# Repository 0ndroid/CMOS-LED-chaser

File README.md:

# CMOS-LED-chaser
LED chaser board with control logic built of discrete transistors

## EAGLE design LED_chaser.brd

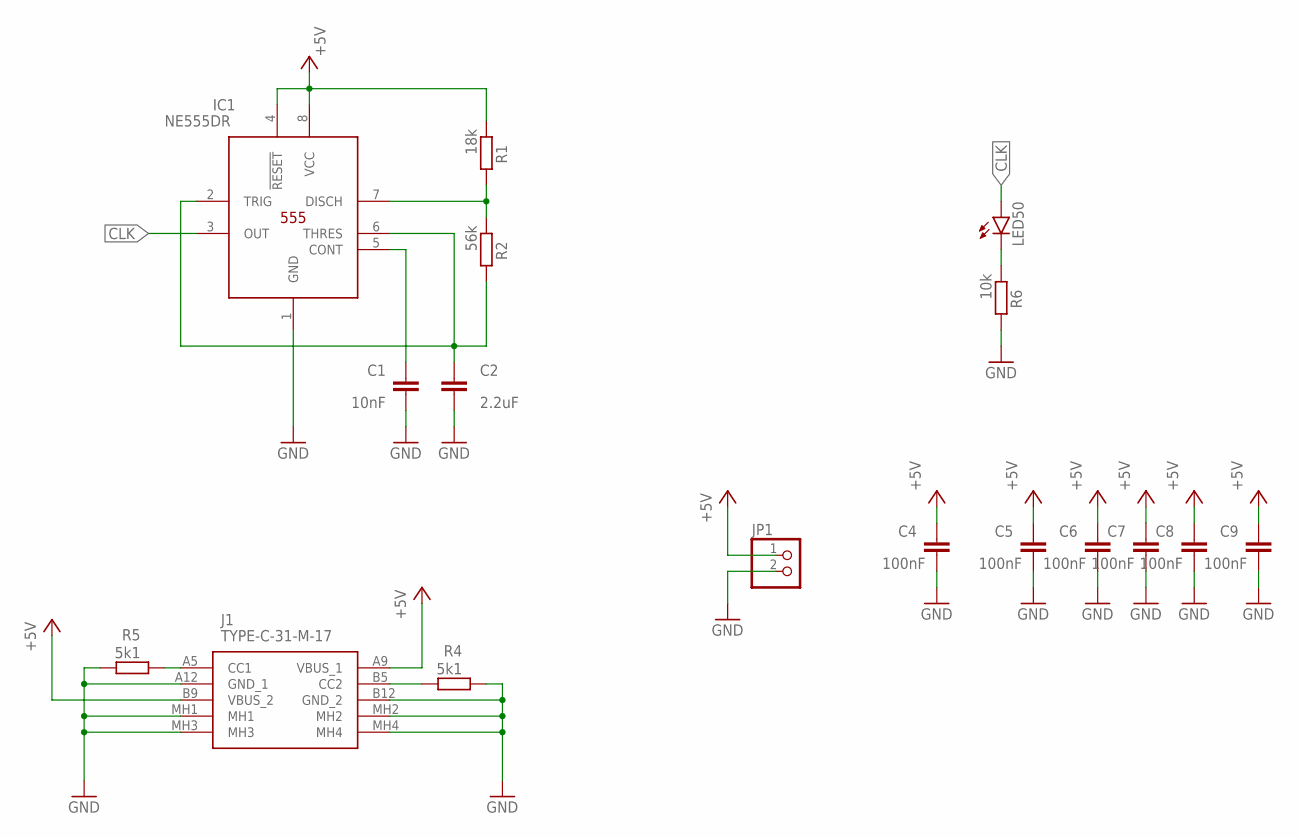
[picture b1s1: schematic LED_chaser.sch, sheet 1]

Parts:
C1: 10nF; C0603
C2: 2.2uF; C0603
C4, C5, C6, C7, C8, C9: 100nF; C0603
IC1: NE555DR; SOIC127P600X175-8N
J1: TYPE-C-31-M-17; TYPEC31M17
JP1: PINHD-1X2; 1X02
LED50: LEDCHIP-LED0603; CHIP-LED0603
R1: 18k; R0603
R2: 56k; R0603
R4, R5: 5k1; R0603
R6: 10k; R0603

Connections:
+5V: C4.1, C5.1, C6.1, C7.1, C8.1, C9.1, IC1.4 (!RESET), IC1.8 (VCC), J1.A9 (VBUS_1), J1.B9 (VBUS_2), JP1.1, R1.1; also elsewhere on the board
CLK: IC1.3 (OUT), LED50.A; also elsewhere on the board
GND: C1.2, C2.2, C4.2, C5.2, C6.2, C7.2, C8.2, C9.2, IC1.1 (GND), J1.A12 (GND_1), J1.B12 (GND_2), J1.MH1, J1.MH2, J1.MH3, J1.MH4, JP1.2, R4.1, R5.2, R6.2; also elsewhere on the board
unnamed: LED50.C, R6.1
unnamed: IC1.7 (DISCH), R1.2, R2.1
unnamed: C1.1, IC1.5 (CONT)
unnamed: C2.1, IC1.2 (TRIG), IC1.6 (THRES), R2.2
unnamed: J1.A5 (CC1), R5.1
unnamed: J1.B5 (CC2), R4.2

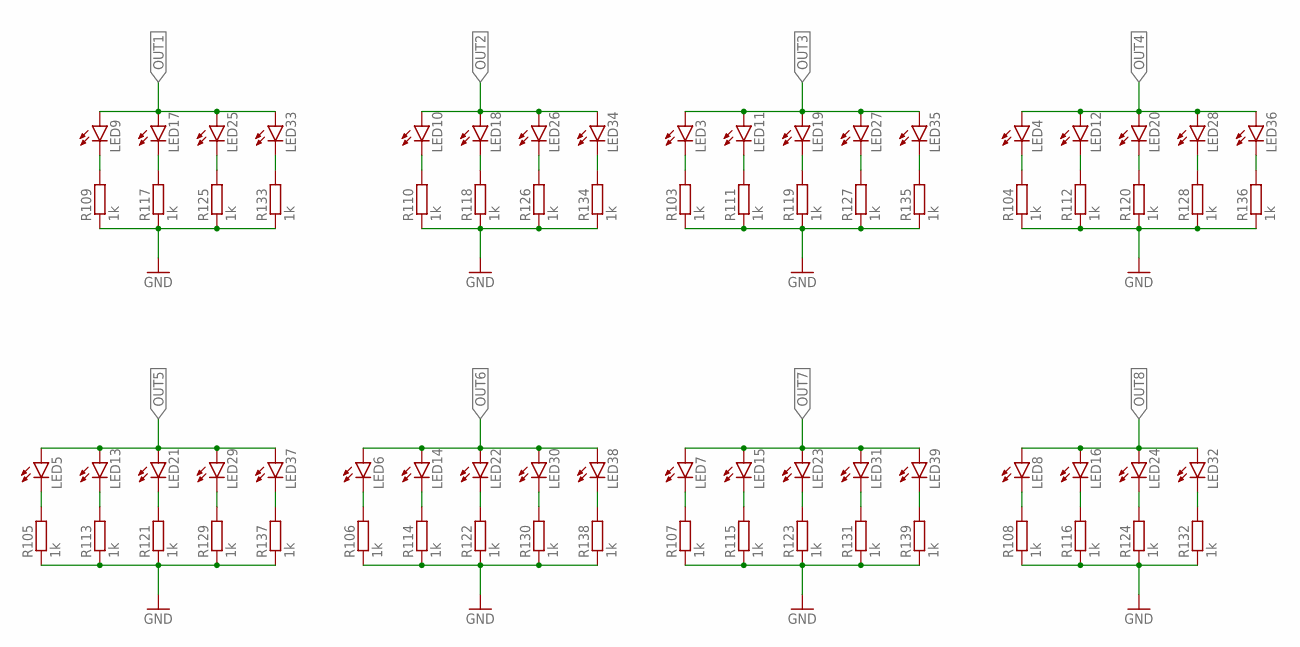
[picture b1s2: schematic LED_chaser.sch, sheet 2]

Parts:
LED3, LED4, LED5, LED6, LED7, LED8, LED9, LED10, LED11, LED12, LED13, LED14, LED15, LED16, LED17, LED18, LED19, LED20, LED21, LED22, LED23, LED24, LED25, LED26, LED27, LED28, LED29, LED30, LED31, LED32, LED33, LED34, LED35, LED36, LED37, LED38, LED39: LEDCHIPLED_1206; CHIPLED_1206
R103, R104, R105, R106, R107, R108, R109, R110, R111, R112, R113, R114, R115, R116, R117, R118, R119, R120, R121, R122, R123, R124, R125, R126, R127, R128, R129, R130, R131, R132, R133, R134, R135, R136, R137, R138, R139: 1k; R0603

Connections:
GND: R103.1, R104.1, R105.1, R106.1, R107.1, R108.1, R109.1, R110.1, R111.1, R112.1, R113.1, R114.1, R115.1, R116.1, R117.1, R118.1, R119.1, R120.1, R121.1, R122.1, R123.1, R124.1, R125.1, R126.1, R127.1, R128.1, R129.1, R130.1, R131.1, R132.1, R133.1, R134.1, R135.1, R136.1, R137.1, R138.1, R139.1; also elsewhere on the board
unnamed: LED9.C, R109.2
unnamed: LED17.C, R117.2
unnamed: LED25.C, R125.2
unnamed: LED33.C, R133.2
unnamed: LED6.C, R106.2
unnamed: LED14.C, R114.2
unnamed: LED22.C, R122.2
unnamed: LED30.C, R130.2
unnamed: LED38.C, R138.2
unnamed: LED7.C, R107.2
unnamed: LED15.C, R115.2
unnamed: LED23.C, R123.2
unnamed: LED31.C, R131.2
unnamed: LED39.C, R139.2
unnamed: LED5.C, R105.2
unnamed: LED13.C, R113.2
unnamed: LED21.C, R121.2
unnamed: LED29.C, R129.2
unnamed: LED37.C, R137.2
unnamed: LED8.C, R108.2
unnamed: LED16.C, R116.2
unnamed: LED24.C, R124.2
unnamed: LED32.C, R132.2
unnamed: LED10.C, R110.2
unnamed: LED18.C, R118.2
unnamed: LED26.C, R126.2
unnamed: LED34.C, R134.2
unnamed: LED3.C, R103.2
unnamed: LED11.C, R111.2
unnamed: LED19.C, R119.2
unnamed: LED27.C, R127.2
unnamed: LED35.C, R135.2
unnamed: LED4.C, R104.2
unnamed: LED12.C, R112.2
unnamed: LED20.C, R120.2
unnamed: LED28.C, R128.2
unnamed: LED36.C, R136.2
OUT1: LED9.A, LED17.A, LED25.A, LED33.A; also elsewhere on the board
OUT2: LED10.A, LED18.A, LED26.A, LED34.A; also elsewhere on the board
OUT3: LED3.A, LED11.A, LED19.A, LED27.A, LED35.A; also elsewhere on the board
OUT4: LED4.A, LED12.A, LED20.A, LED28.A, LED36.A; also elsewhere on the board
OUT5: LED5.A, LED13.A, LED21.A, LED29.A, LED37.A; also elsewhere on the board
OUT6: LED6.A, LED14.A, LED22.A, LED30.A, LED38.A; also elsewhere on the board
OUT7: LED7.A, LED15.A, LED23.A, LED31.A, LED39.A; also elsewhere on the board
OUT8: LED8.A, LED16.A, LED24.A, LED32.A; also elsewhere on the board

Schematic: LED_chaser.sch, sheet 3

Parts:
T17, T19, T21, T23, T25, T27, T29, T31, T33, T35, T37, T39, T41, T43, T45, T47, T49, T51, T53, T55, T57, T59, T61, T63, T65, T67, T69, T71, T73, T75, T77, T79, T97, T99, T101, T103, T105, T107, T109, T111, T129, T131, T133, T135, T137, T139, T141, T143, T161, T163, T165, T167, T169, T171, T173, T175: 2N7002; SOT-23
T18, T20, T22, T24, T26, T28, T30, T32, T34, T36, T38, T40, T42, T44, T46, T48, T50, T52, T54, T56, T58, T60, T62, T64, T66, T68, T70, T72, T74, T76, T78, T80, T98, T100, T102, T104, T106, T108, T110, T112, T130, T132, T134, T136, T138, T140, T142, T144, T162, T164, T166, T168, T170, T172, T174, T176: BSS84; SOT-23

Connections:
+5V: T18.2 (S), T20.2 (S), T22.2 (S), T24.2 (S), T26.2 (S), T28.2 (S), T30.2 (S), T32.2 (S), T34.2 (S), T36.2 (S), T38.2 (S), T40.2 (S), T42.2 (S), T44.2 (S), T46.2 (S), T48.2 (S), T50.2 (S), T52.2 (S), T54.2 (S), T56.2 (S), T58.2 (S), T60.2 (S), T62.2 (S), T64.2 (S), T66.2 (S), T68.2 (S), T70.2 (S), T72.2 (S), T74.2 (S), T76.2 (S), T78.2 (S), T80.2 (S), T98.2 (S), T100.2 (S), T102.2 (S), T104.2 (S), T106.2 (S), T108.2 (S), T110.2 (S), T112.2 (S), T130.2 (S), T132.2 (S), T134.2 (S), T136.2 (S), T138.2 (S), T140.2 (S), T142.2 (S), T144.2 (S), T162.2 (S), T164.2 (S), T166.2 (S), T168.2 (S), T170.2 (S), T172.2 (S), T174.2 (S), T176.2 (S); also elsewhere on the board
CLK: T19.3 (G), T20.3 (G), T21.3 (G), T22.3 (G), T51.3 (G), T52.3 (G), T53.3 (G), T54.3 (G), T67.3 (G), T68.3 (G), T69.3 (G), T70.3 (G), T131.3 (G), T132.3 (G), T133.3 (G), T134.3 (G); also elsewhere on the board
CLK_INV: T35.3 (G), T36.3 (G), T37.3 (G), T38.3 (G), T99.3 (G), T100.3 (G), T101.3 (G), T102.3 (G), T163.3 (G), T164.3 (G), T165.3 (G), T166.3 (G); also elsewhere on the board
GND: T19.2 (S), T23.2 (S), T27.2 (S), T31.2 (S), T35.2 (S), T39.2 (S), T43.2 (S), T47.2 (S), T51.2 (S), T55.2 (S), T59.2 (S), T63.2 (S), T67.2 (S), T71.2 (S), T75.2 (S), T79.2 (S), T99.2 (S), T103.2 (S), T107.2 (S), T111.2 (S), T131.2 (S), T135.2 (S), T139.2 (S), T143.2 (S), T163.2 (S), T167.2 (S), T171.2 (S), T175.2 (S); also elsewhere on the board
unnamed 4: T23.3 (G), T24.3 (G); also elsewhere on the board
unnamed: T27.3 (G), T28.3 (G), T29.1 (D), T30.1 (D), T32.1 (D), T39.3 (G), T40.3 (G)
unnamed: T17.2 (S), T19.1 (D)
unnamed: T21.2 (S), T23.1 (D)
unnamed: T25.2 (S), T27.1 (D)
unnamed: T29.2 (S), T31.1 (D)
unnamed: T17.1 (D), T18.1 (D), T20.1 (D), T25.3 (G), T26.3 (G)
unnamed: T21.1 (D), T22.1 (D), T24.1 (D), T31.3 (G), T32.3 (G)
unnamed: T43.3 (G), T44.3 (G), T45.1 (D), T46.1 (D), T48.1 (D), T71.3 (G), T72.3 (G)
unnamed: T33.2 (S), T35.1 (D)
unnamed: T37.2 (S), T39.1 (D)
unnamed: T41.2 (S), T43.1 (D)
unnamed: T45.2 (S), T47.1 (D)
unnamed: T33.1 (D), T34.1 (D), T36.1 (D), T41.3 (G), T42.3 (G)
unnamed: T37.1 (D), T38.1 (D), T40.1 (D), T47.3 (G), T48.3 (G)
unnamed: T59.3 (G), T60.3 (G), T61.1 (D), T62.1 (D), T64.1 (D)
unnamed: T49.2 (S), T51.1 (D)
unnamed: T53.2 (S), T55.1 (D)
unnamed: T57.2 (S), T59.1 (D)
unnamed: T61.2 (S), T63.1 (D)
unnamed: T49.1 (D), T50.1 (D), T52.1 (D), T57.3 (G), T58.3 (G)
unnamed: T53.1 (D), T54.1 (D), T56.1 (D), T63.3 (G), T64.3 (G)
unnamed: T75.3 (G), T76.3 (G), T77.1 (D), T78.1 (D), T80.1 (D), T103.3 (G), T104.3 (G)
unnamed: T65.2 (S), T67.1 (D)
unnamed: T69.2 (S), T71.1 (D)
unnamed: T73.2 (S), T75.1 (D)
unnamed: T77.2 (S), T79.1 (D)
unnamed: T65.1 (D), T66.1 (D), T68.1 (D), T73.3 (G), T74.3 (G)
unnamed: T69.1 (D), T70.1 (D), T72.1 (D), T79.3 (G), T80.3 (G)
unnamed: T107.3 (G), T108.3 (G), T109.1 (D), T110.1 (D), T112.1 (D), T135.3 (G), T136.3 (G)
unnamed: T97.2 (S), T99.1 (D)
unnamed: T101.2 (S), T103.1 (D)
unnamed: T105.2 (S), T107.1 (D)
unnamed: T109.2 (S), T111.1 (D)
unnamed: T97.1 (D), T98.1 (D), T100.1 (D), T105.3 (G), T106.3 (G)
unnamed: T101.1 (D), T102.1 (D), T104.1 (D), T111.3 (G), T112.3 (G)
unnamed: T139.3 (G), T140.3 (G), T141.1 (D), T142.1 (D), T144.1 (D), T167.3 (G), T168.3 (G)
unnamed: T129.2 (S), T131.1 (D)
unnamed: T133.2 (S), T135.1 (D)
unnamed: T137.2 (S), T139.1 (D)
unnamed: T141.2 (S), T143.1 (D)
unnamed: T129.1 (D), T130.1 (D), T132.1 (D), T137.3 (G), T138.3 (G)
unnamed: T133.1 (D), T134.1 (D), T136.1 (D), T143.3 (G), T144.3 (G)
unnamed: T55.3 (G), T56.3 (G), T171.3 (G), T172.3 (G), T173.1 (D), T174.1 (D), T176.1 (D)
unnamed: T161.2 (S), T163.1 (D)
unnamed: T165.2 (S), T167.1 (D)
unnamed: T169.2 (S), T171.1 (D)
unnamed: T173.2 (S), T175.1 (D)
unnamed: T161.1 (D), T162.1 (D), T164.1 (D), T169.3 (G), T170.3 (G)
unnamed: T165.1 (D), T166.1 (D), T168.1 (D), T175.3 (G), T176.3 (G)
OUT1: T17.3 (G), T18.3 (G); also elsewhere on the board
OUT2: T25.1 (D), T26.1 (D), T28.1 (D), T29.3 (G), T30.3 (G), T33.3 (G), T34.3 (G); also elsewhere on the board
OUT3: T41.1 (D), T42.1 (D), T44.1 (D), T45.3 (G), T46.3 (G), T65.3 (G), T66.3 (G); also elsewhere on the board
OUT4: T73.1 (D), T74.1 (D), T76.1 (D), T77.3 (G), T78.3 (G), T97.3 (G), T98.3 (G); also elsewhere on the board
OUT5: T105.1 (D), T106.1 (D), T108.1 (D), T109.3 (G), T110.3 (G), T129.3 (G), T130.3 (G); also elsewhere on the board
OUT6: T137.1 (D), T138.1 (D), T140.1 (D), T141.3 (G), T142.3 (G), T161.3 (G), T162.3 (G); also elsewhere on the board
OUT7: T49.3 (G), T50.3 (G), T169.1 (D), T170.1 (D), T172.1 (D), T173.3 (G), T174.3 (G); also elsewhere on the board
OUT8: T57.1 (D), T58.1 (D), T60.1 (D), T61.3 (G), T62.3 (G); also elsewhere on the board

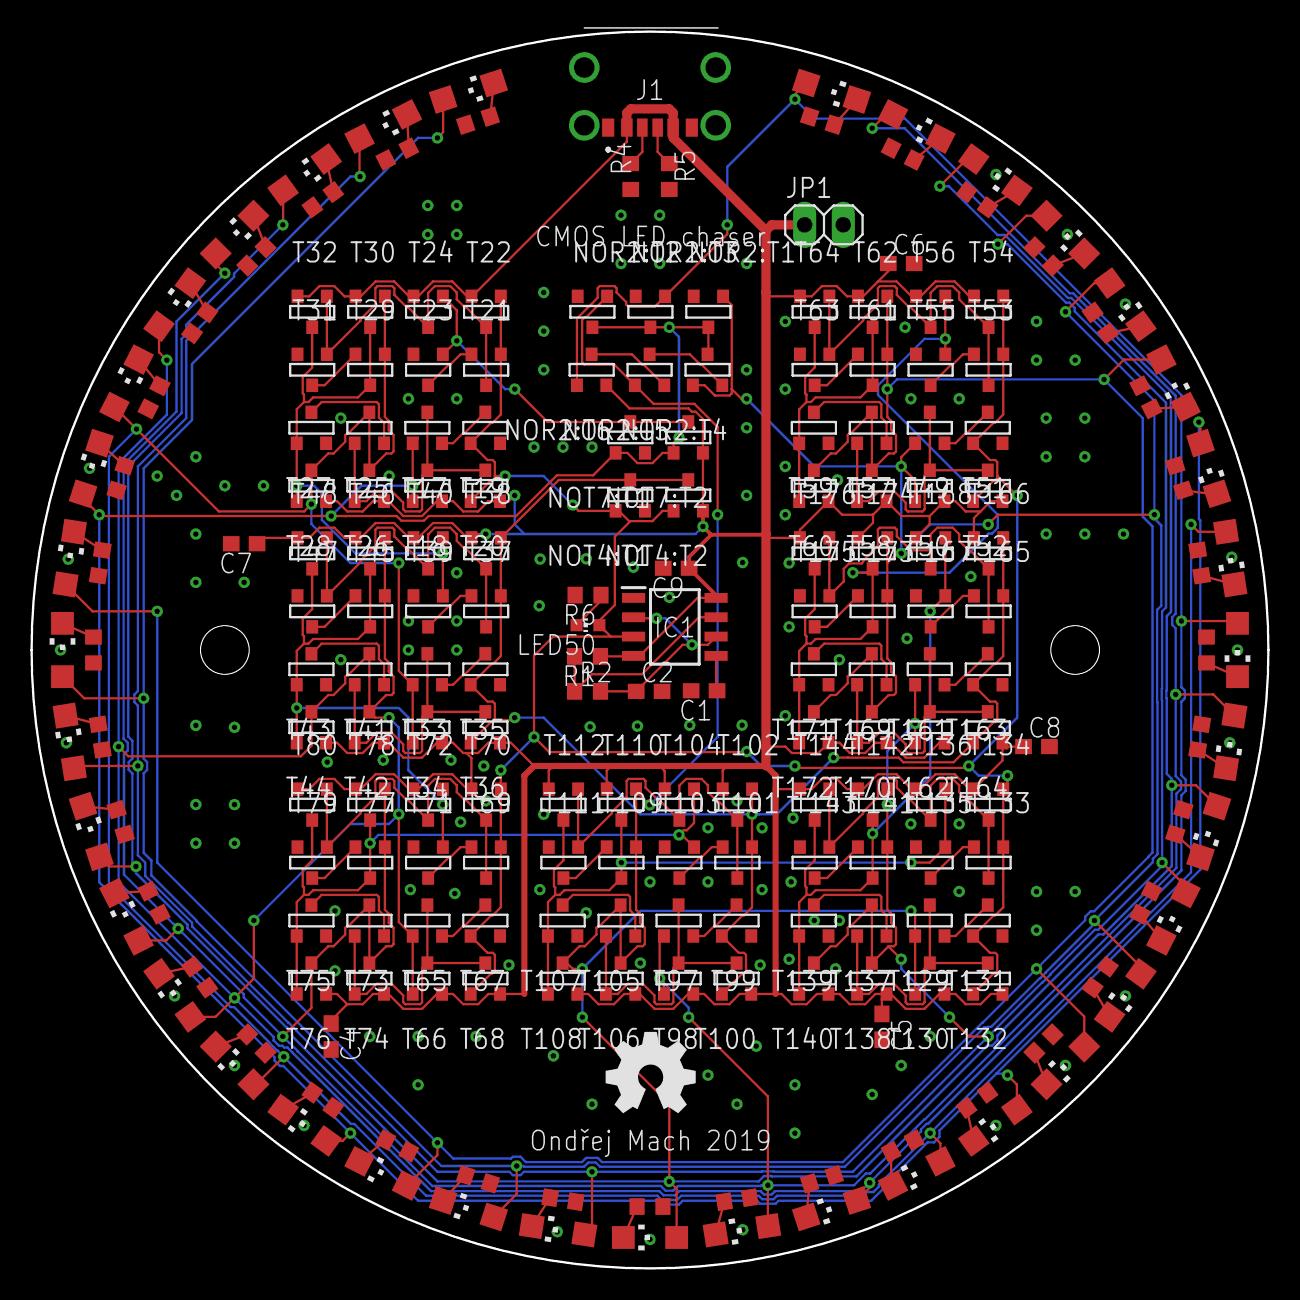
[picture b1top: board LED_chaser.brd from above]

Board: 2 copper layers, 81.3 x 81.3 mm, 213 parts (0 on the bottom side), 107 nets.

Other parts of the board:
NOR2:T1, NOR2:T2, NOR2:T3: 2N7002; SOT-23
NOR2:T4, NOR2:T5, NOR2:T6: BSS84; SOT-23
NOT4:T1, NOT7:T1: 2N7002; SOT-23
NOT4:T2, NOT7:T2: BSS84; SOT-23

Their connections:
+5V: NOR2:T6.2, NOT4:T2.2, NOT7:T2.2; also elsewhere on the board
CLK: NOT4:T1.3, NOT4:T2.3; also elsewhere on the board
CLK_INV: NOT4:T1.1, NOT4:T2.1; also elsewhere on the board
GND: NOR2:T1.2, NOR2:T2.2, NOR2:T3.2, NOT4:T1.2, NOT7:T1.2; also elsewhere on the board
unnamed 4: NOT7:T1.1, NOT7:T2.1; also elsewhere on the board
NOR2:N$1: NOR2:T4.2, NOR2:T5.1
NOR2:N$2: NOR2:T5.2, NOR2:T6.1
OUT1: NOR2:T1.1, NOR2:T2.1, NOR2:T3.1, NOR2:T4.1, NOT7:T1.3, NOT7:T2.3; also elsewhere on the board
OUT3: NOR2:T3.3, NOR2:T6.3; also elsewhere on the board
OUT5: NOR2:T2.3, NOR2:T5.3; also elsewhere on the board
OUT7: NOR2:T1.3, NOR2:T4.3; also elsewhere on the board
